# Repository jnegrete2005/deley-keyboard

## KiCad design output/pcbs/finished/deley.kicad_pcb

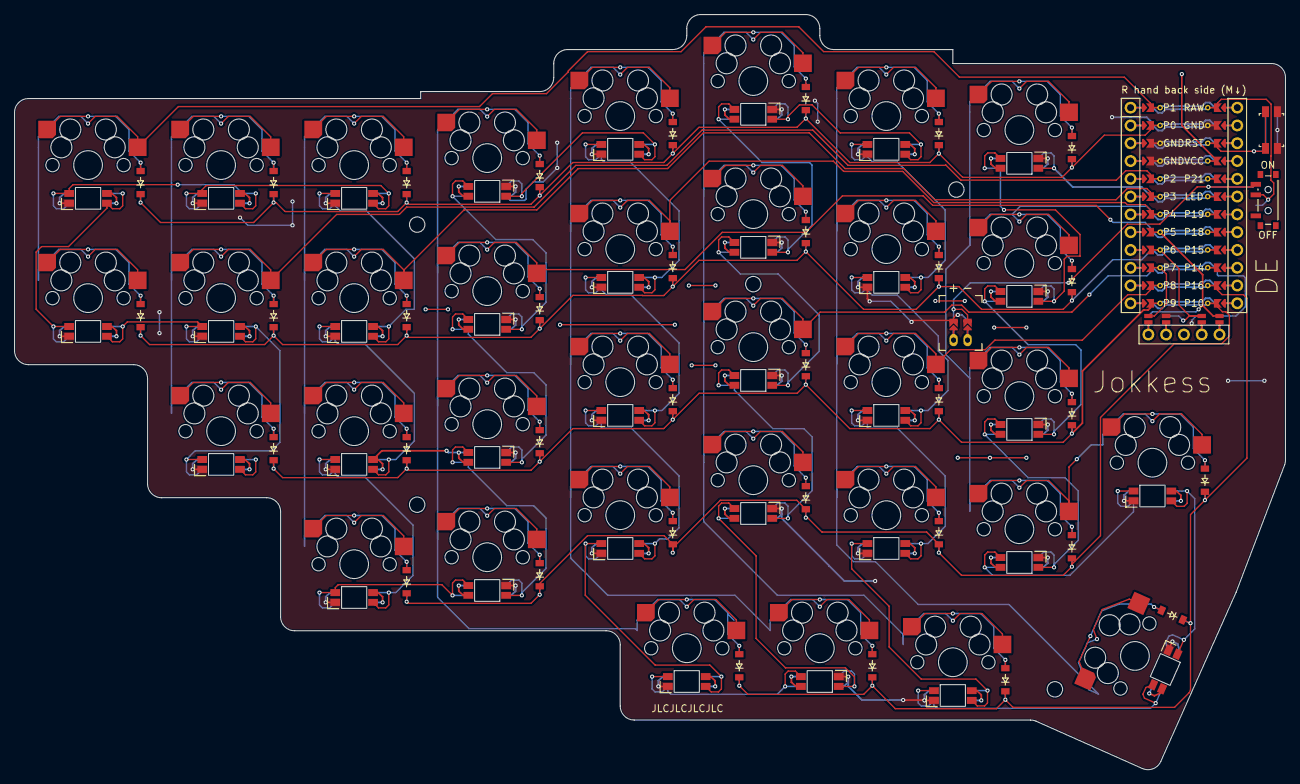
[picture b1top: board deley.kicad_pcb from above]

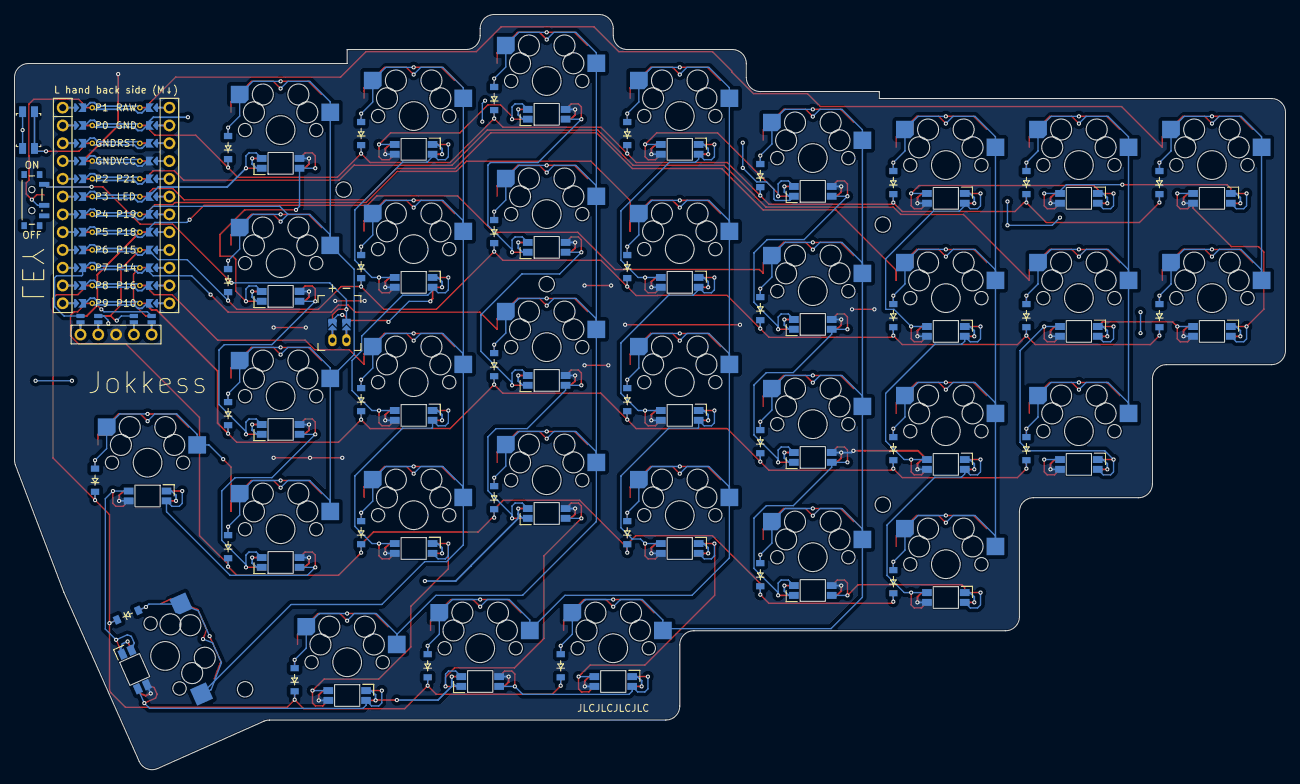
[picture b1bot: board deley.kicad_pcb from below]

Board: 2 copper layers, 181.5 x 107.8 mm, 112 parts (69 on the bottom side), 95 nets.

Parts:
D1, D2, D3, D4, D5, D6, D7, D8, D9, D10, D11, D12, D13, D14, D15, D16, D17, D18, D19, D20, D21, D22, D23, D24, D25, D26, D27, D28, D29, D30, D31, D32, D33, D34: diode_tht_sod123
DISP1: display_nice_view
JST1: battery_connector_jst_ph_2
LED1, LED2, LED3, LED4, LED5, LED6, LED7, LED8, LED9, LED10, LED11, LED12, LED13, LED14, LED15, LED16, LED17, LED18, LED19, LED20, LED21, LED22, LED23, LED24, LED25, LED26, LED27, LED28, LED29, LED30, LED31, LED32, LED33, LED34: led_SK6812mini-e (per-key, reversible)
MCU1: mcu_supermini_nrf52840
MH1, MH2, MH3, MH4, MH5: mounting_hole_npth
PWR1: power_switch_smd_side
RST1: reset_switch_smd_side
S1, S2, S3, S4, S5, S6, S7, S8, S9, S10, S11, S12, S13, S14, S15, S16, S17, S18, S19, S20, S21, S22, S23, S24, S25, S26, S27, S28, S29, S30, S31, S32, S33, S34: switch_mx

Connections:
DISP1_1: DISP1.1, DISP1.10, DISP1.23
DISP1_2: DISP1.2, DISP1.11, DISP1.22
DISP1_4: DISP1.4, DISP1.12, DISP1.21
DISP1_5: DISP1.5, DISP1.13, DISP1.20
GND: DISP1.15, DISP1.25, JST1.2, LED1.3, LED2.3, LED3.3, LED4.3, LED5.3, LED6.3, LED7.3, LED8.3, LED9.3, LED10.3, LED11.3, LED12.3, LED13.3, LED14.3, LED15.3, LED16.3, LED17.3, LED18.3, LED19.3, LED20.3, LED21.3, LED22.3, LED23.3, LED24.3, LED25.3, LED26.3, LED27.3, LED28.3, LED29.3, LED30.3, LED31.3, LED32.3, LED33.3, LED34.3, MCU1.102, MCU1.121, MCU1.122, RST1.1, RST1.3
JST1_1: JST1.11, JST1.21, JST1.31
JST1_2: JST1.12, JST1.22, JST1.32
LED_0: LED32.4, MCU1.106
LED_1: LED31.4, LED32.2
LED_2: LED30.4, LED31.2
LED_3: LED29.4, LED30.2
LED_4: LED20.4, LED29.2
LED_5: LED20.2, LED34.4
LED_6: LED19.4, LED34.2
LED_7: LED14.4, LED19.2
LED_8: LED14.2, LED15.4
LED_9: LED15.2, LED16.4
LED_10: LED16.2, LED17.4
LED_11: LED17.2, LED28.4
LED_12: LED27.4, LED28.2
LED_13: LED26.4, LED27.2
LED_14: LED25.4, LED26.2
LED_15: LED25.2, LED33.4
LED_16: LED18.4, LED33.2
LED_17: LED10.4, LED18.2
LED_18: LED10.2, LED11.4
LED_19: LED11.2, LED12.4
LED_20: LED12.2, LED13.4
LED_21: LED13.2, LED24.4
LED_22: LED23.4, LED24.2
LED_23: LED22.4, LED23.2
LED_24: LED21.4, LED22.2
LED_25: LED6.4, LED21.2
LED_26: LED6.2, LED7.4
LED_27: LED7.2, LED8.4
LED_28: LED8.2, LED9.4
LED_29: LED5.4, LED9.2
LED_30: LED2.4, LED5.2
LED_31: LED1.4, LED2.2
LED_32: LED1.2, LED4.4
LED_33: LED3.4, LED4.2
P0: D2.1, D5.1, D9.1, D13.1, D17.1, D21.1, D25.1, D29.1, MCU1.123
P1: MCU1.124, S1.1, S2.1
P2: MCU1.120, S3.1, S4.1, S5.1
P3: MCU1.119, S6.1, S7.1, S8.1, S9.1
P4: MCU1.118, S14.1, S15.1, S16.1, S17.1, S31.1
P5: DISP1.17, DISP1.27, MCU1.117
P6: DISP1.16, DISP1.26, MCU1.116
P7: DISP1.14, DISP1.24, MCU1.115
P8: MCU1.114, S22.1, S23.1, S24.1, S25.1, S33.1
P9: D3.1, D7.1, D11.1, D15.1, D19.1, D23.1, D27.1, MCU1.113
P10: D6.1, D10.1, D14.1, D18.1, D22.1, D26.1, MCU1.112
P14: MCU1.110, S18.1, S19.1, S20.1, S21.1, S32.1
P15: D1.1, D4.1, D8.1, D12.1, D16.1, D20.1, D24.1, D28.1, MCU1.109
P16: D30.1, D31.1, D32.1, D33.1, D34.1, MCU1.111
P18: MCU1.108, S10.1, S11.1, S12.1, S13.1, S30.1
P19: MCU1.107, S26.1, S27.1, S28.1, S29.1, S34.1
RAW: MCU1.101, PWR1.2
RST: MCU1.103, RST1.2, RST1.4
VCC: DISP1.3, LED1.1, LED2.1, LED3.1, LED4.1, LED5.1, LED6.1, LED7.1, LED8.1, LED9.1, LED10.1, LED11.1, LED12.1, LED13.1, LED14.1, LED15.1, LED16.1, LED17.1, LED18.1, LED19.1, LED20.1, LED21.1, LED22.1, LED23.1, LED24.1, LED25.1, LED26.1, LED27.1, LED28.1, LED29.1, LED30.1, LED31.1, LED32.1, LED33.1, LED34.1, MCU1.104
double_bottom: D33.2, S33.2
far_bottom: D32.2, S32.2
home_bottom: D31.2, S31.2
index_bottom: D22.2, S22.2
index_home: D23.2, S23.2
index_number: D25.2, S25.2
index_top: D24.2, S24.2
inner_bottom: D26.2, S26.2
inner_home: D27.2, S27.2
inner_number: D29.2, S29.2
inner_top: D28.2, S28.2
main_main: D34.2, S34.2
middle_bottom: D18.2, S18.2
middle_home: D19.2, S19.2
middle_number: D21.2, S21.2
middle_top: D20.2, S20.2
near_bottom: D30.2, S30.2
outer2_home: D3.2, S3.2
outer2_number: D5.2, S5.2
outer2_top: D4.2, S4.2
outer3_number: D2.2, S2.2
outer3_top: D1.2, S1.2
outer_bottom: D6.2, S6.2
outer_home: D7.2, S7.2
outer_number: D9.2, S9.2
outer_top: D8.2, S8.2
pinky_bottom: D10.2, S10.2
pinky_home: D11.2, S11.2
pinky_number: D13.2, S13.2
pinky_top: D12.2, S12.2
pos: JST1.1, PWR1.1, PWR1.3
ring_bottom: D14.2, S14.2
ring_home: D15.2, S15.2
ring_number: D17.2, S17.2
ring_top: D16.2, S16.2

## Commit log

2024-12-22 Left v0.1-alpha
2024-12-22 Add JLC text to board
2024-12-22 Rename build and open scripts
2025-01-09 build deley
2025-01-09 move deley to finished
